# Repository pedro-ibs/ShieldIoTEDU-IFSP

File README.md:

# Shield IoT EDU-IFSP
Shield IoT EDU-IFSP, placa  desenvolvimento e estudos utilizando o ESP32

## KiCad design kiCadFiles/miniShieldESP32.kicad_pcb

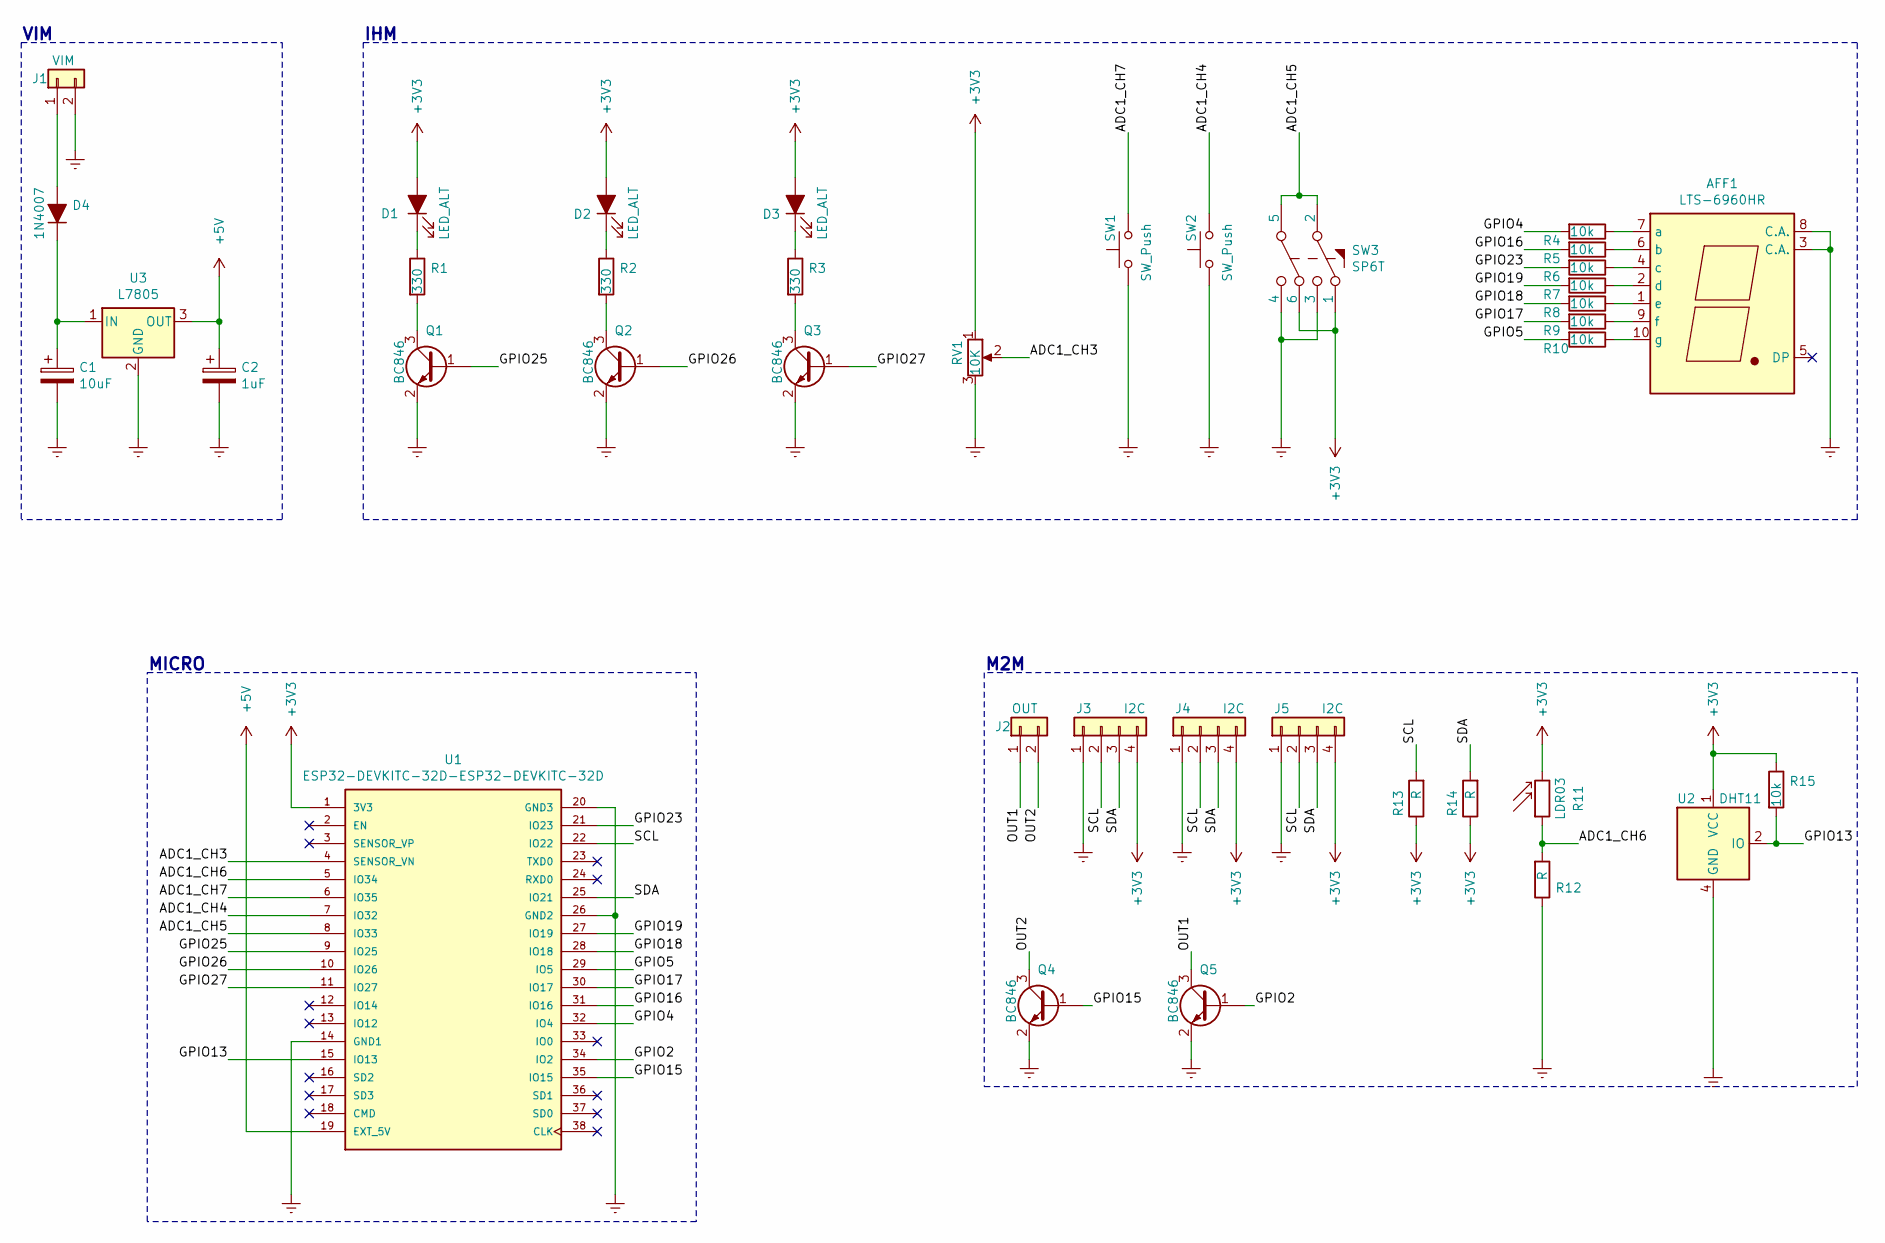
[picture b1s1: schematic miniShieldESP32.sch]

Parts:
AFF1: LTS-6960HR; 7SegmentLED_LTS6760_LTS6780
C1: 10uF; CP_Radial_D5.0mm_P2.50mm
C2: 1uF; CP_Radial_D5.0mm_P2.50mm
D1, D2, D3: LED_ALT; LED_D3.0mm
D4: 1N4007; D_DO-15_P3.81mm_Vertical_KathodeUp
J1: VIM; AK300-2
J2: OUT; AK300-2
J3, J4, J5: I2C; Molex_KK-254_AE-6410-04A_1x04_P2.54mm_Vertical
Q1, Q2, Q3, Q4, Q5: BC846; TO-92_Inline_Wide
R1, R2, R3: 330; Resistor_Vertical_RM3mm
R4, R5, R6, R7, R8, R9, R10, R15: 10k; Resistor_Vertical_RM3mm
R11: LDR03; LDR3mm
R12, R14: R; R_Axial_DIN0207_L6.3mm_D2.5mm_P10.16mm_Horizontal
R13: R; Resistor_Vertical_RM3mm
RV1: 10K; Potentiometer_Alps-RK16-single_largePads
SW1, SW2: SW_Push; SW_PUSH_6mm_2P
SW3: SP6T; SW_PUSH_x2
U1: ESP32-DEVKITC-32D-ESP32-DEVKITC-32D; MODULE_ESP32-DEVKITC-32D; PARTREV 4
U2: DHT11; Aosong_DHT11_5.5x12.0_P2.54mm
U3: L7805; TO-220F-3_Vertical

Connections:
+3V3: D1.2 (A), D2.2 (A), D3.2 (A), J3.4, J4.4, J5.4, R11.2, R13.1, R14.1, R15.1, RV1.1, SW3.1, SW3.6, U1.1 (3V3), U2.1 (VCC)
+5V: C2.1, U1.19 (EXT_5V), U3.3 (OUT)
/ADC1_CH3: RV1.2, U1.4 (SENSOR_VN)
/ADC1_CH4: SW2.2, U1.7 (IO32)
/ADC1_CH5: SW3.2, SW3.5, U1.8 (IO33)
/ADC1_CH6: R11.1, R12.2, U1.5 (IO34)
/ADC1_CH7: SW1.2, U1.6 (IO35)
/GPIO2: Q5.1 (B), U1.34 (IO2)
/GPIO4: R4.2, U1.32 (IO4)
/GPIO5: R10.2, U1.29 (IO5)
/GPIO13: R15.2, U1.15 (IO13), U2.2 (IO)
/GPIO15: Q4.1 (B), U1.35 (IO15)
/GPIO16: R5.2, U1.31 (IO16)
/GPIO17: R9.2, U1.30 (IO17)
/GPIO18: R8.2, U1.28 (IO18)
/GPIO19: R7.2, U1.27 (IO19)
/GPIO23: R6.2, U1.21 (IO23)
/GPIO25: Q1.1 (B), U1.9 (IO25)
/GPIO26: Q2.1 (B), U1.10 (IO26)
/GPIO27: Q3.1 (B), U1.11 (IO27)
/OUT1: J2.1, Q5.3 (C)
/OUT2: J2.2, Q4.3 (C)
/SCL: J3.2, J4.2, J5.2, R13.2, U1.22 (IO22)
/SDA: J3.3, J4.3, J5.3, R14.2, U1.25 (IO21)
Earth: AFF1.3 (C.A.), AFF1.8 (C.A.), C1.2, C2.2, J1.2, J3.1, J4.1, J5.1, Q1.2 (E), Q2.2 (E), Q3.2 (E), Q4.2 (E), Q5.2 (E), R12.1, RV1.3, SW1.1, SW2.1, SW3.3, SW3.4, U1.14 (GND1), U1.20 (GND3), U1.26 (GND2), U2.4 (GND), U3.2 (GND)
unnamed: AFF1.1 (e), R8.1
unnamed: AFF1.2 (d), R7.1
unnamed: AFF1.4 (c), R6.1
unnamed: AFF1.6 (b), R5.1
unnamed: AFF1.7 (a), R4.1
unnamed: AFF1.9 (f), R9.1
unnamed: AFF1.10 (g), R10.1
unnamed: C1.1, D4.1 (K), U3.1 (IN)
unnamed: D1.1 (K), R1.1
unnamed: D2.1 (K), R2.1
unnamed: D3.1 (K), R3.1
unnamed: D4.2 (A), J1.1
unnamed: Q1.3 (C), R1.2
unnamed: Q2.3 (C), R2.2
unnamed: Q3.3 (C), R3.2

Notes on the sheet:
M2M
VIM
IHM
MICRO

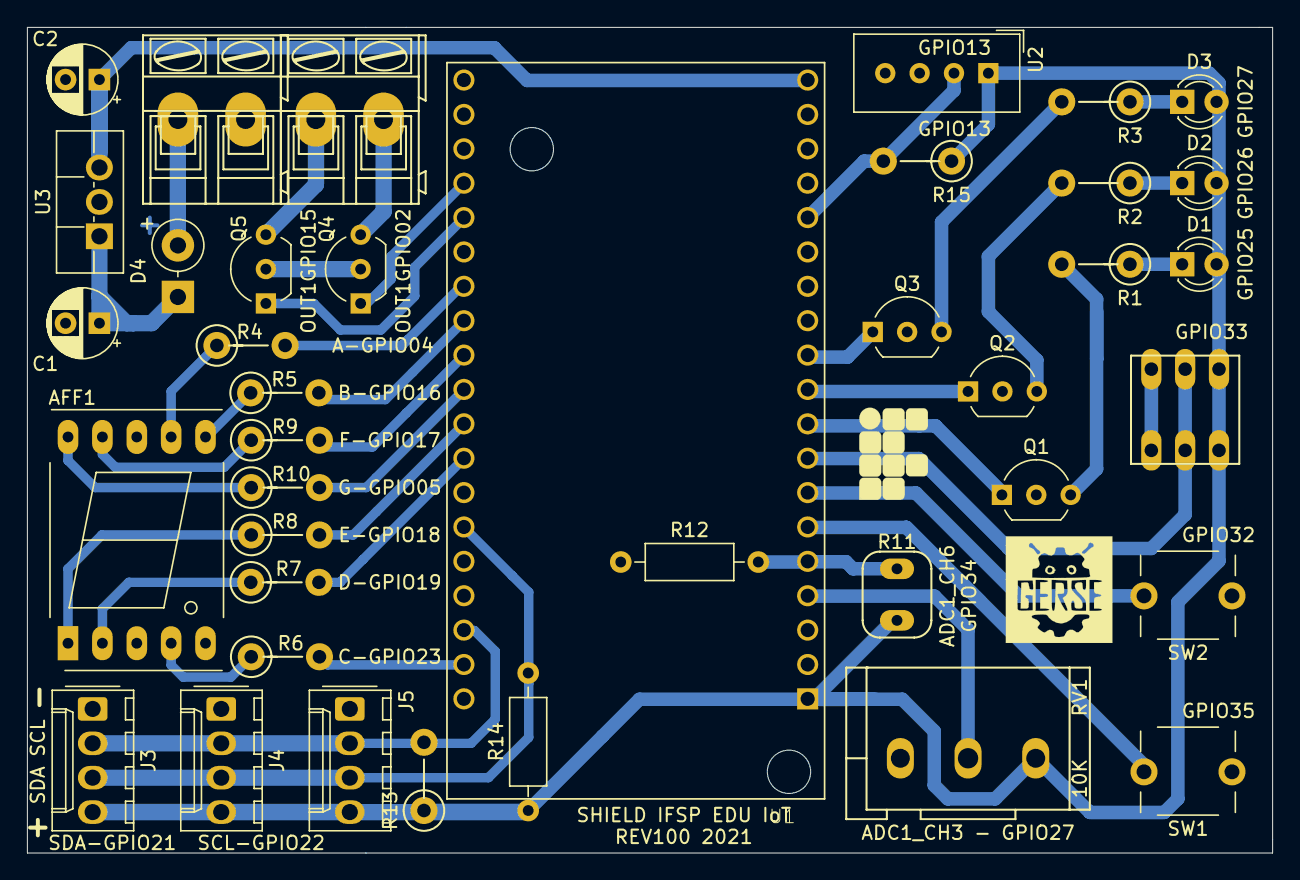
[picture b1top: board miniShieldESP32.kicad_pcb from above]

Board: 2 copper layers, 92.0 x 61.0 mm, 39 parts (0 on the bottom side), 40 nets.

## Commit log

2021-03-10 add files
2021-04-17 arruamdno legendas, lesd e dht11
2021-04-17 gerber
